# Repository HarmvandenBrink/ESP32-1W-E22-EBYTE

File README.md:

# ESP32 1W E22-400M30S / E22-900M30S
ESP32-based EBYTE E22-400M30S / E22-900M30S compatible 1 Watt board

Forked the design, changed it to KiCAD.

## Features:
* Fully compatible with https://github.com/G4lile0/ESP32-OLED-Fossa-GroundStation
* Radio: Ebyte E22-400M30S / E22-900M30S (http://www.ebyte.com/en/product-view-news.aspx?id=454)
  * SX1268 with TCXO
  * 1W external PA
  * Automatic Rx/Tx switching
  * IPX and SMA connectors
* OLED display
* Selectable power source (USB/external jack)
* Status LEDs: power, Rx/Tx, ESP32 IO2
* On-board USB/UART convertor

Forked from https://github.com/jgromes/ESP32-1W-GroundStation which was Eagle

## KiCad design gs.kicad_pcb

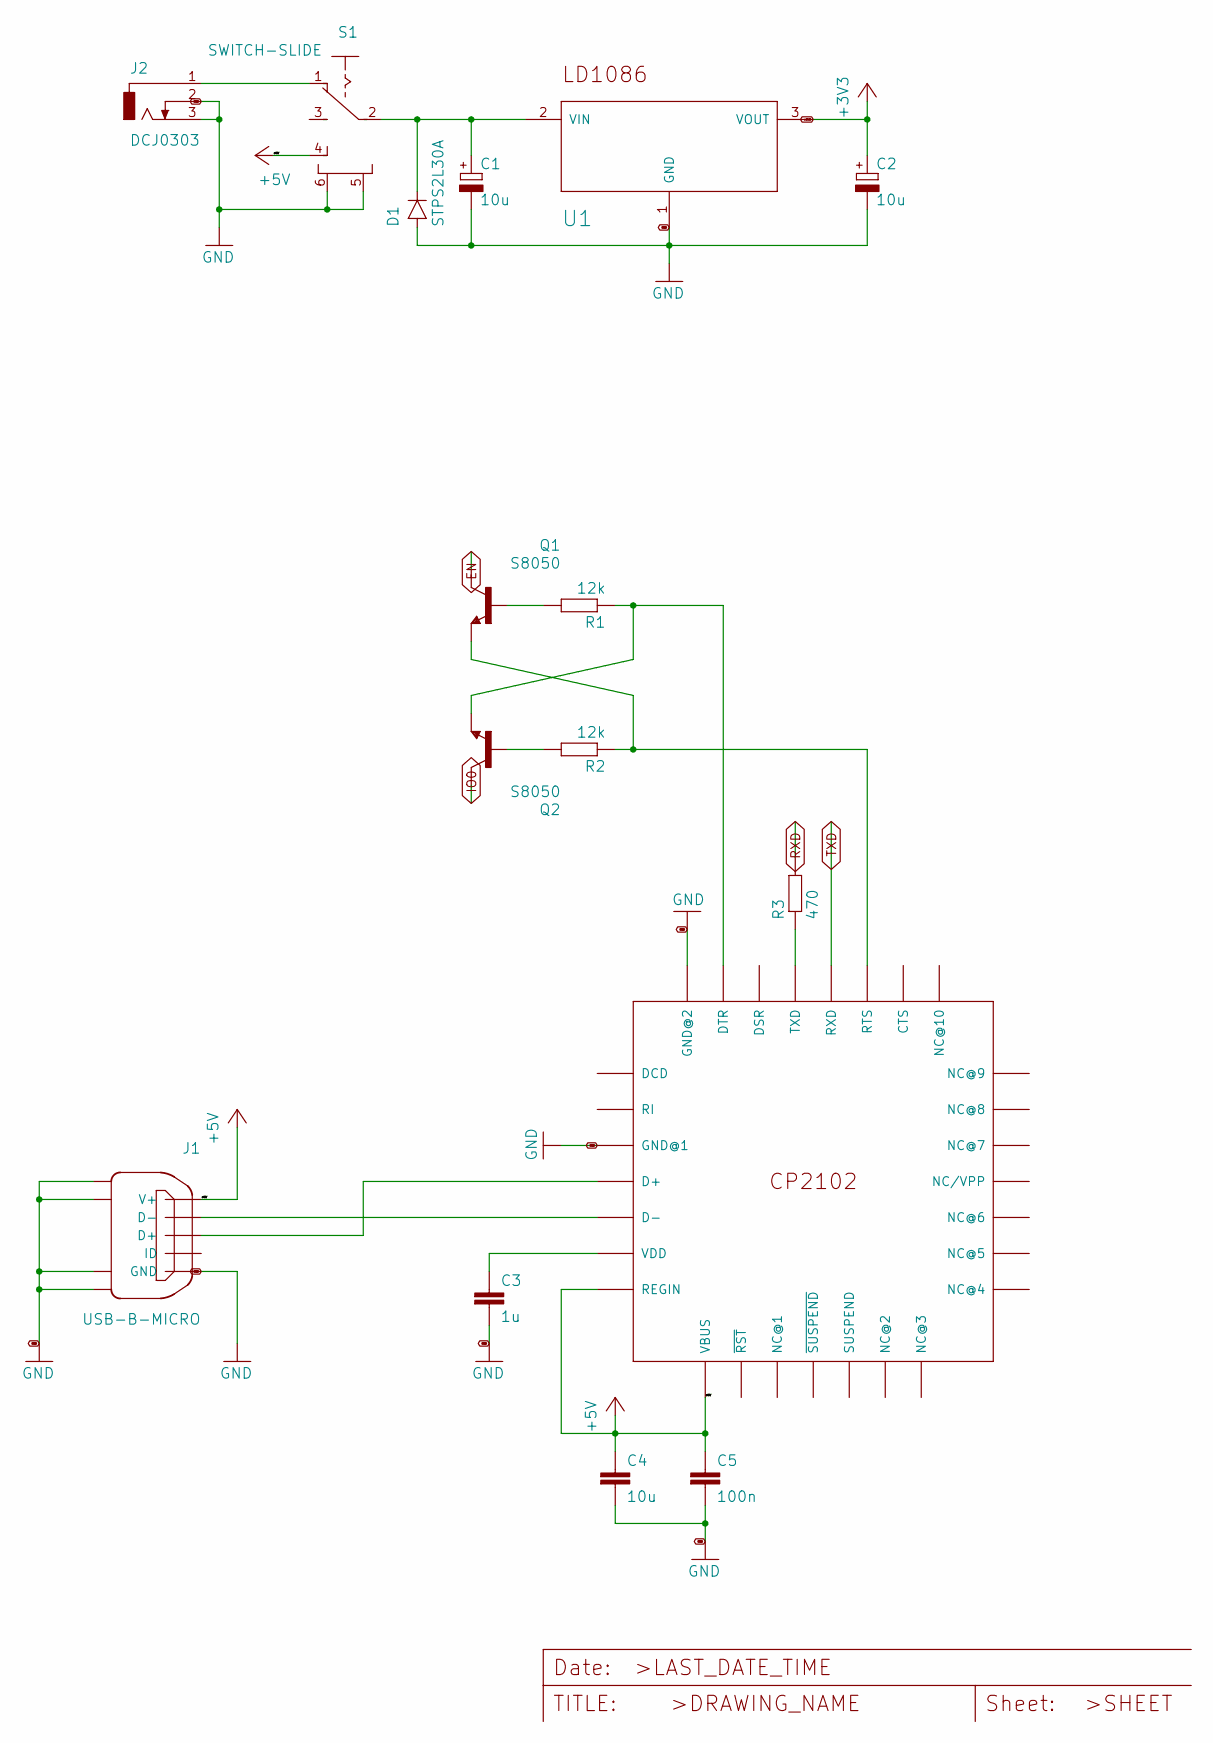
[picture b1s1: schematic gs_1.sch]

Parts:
C1, C2: 10u; SMC_C
C3: 1u; C0805
C4: 10u; C0805
C5: 100n; C0805
D1: STPS2L30A; DIOM4225X245N
J1: USB-B-MICRO
J2: DCJ0303
Q1, Q2: S8050; SOT95P237X110-3N
R1, R2: 12k; R0805
R3: 470; R0805
S1: SWITCH-SLIDE
U1: LD1086DT33TR; TO228P972X240-3N
U2: CP2102; QFN50P500X500X100-29T300N

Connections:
+3V3: C2.+, U1.3 (VOUT); also elsewhere on the board
+5V: C4.1, C5.1, J1.1 (V+), S1.4, U2.7 (REGIN), U2.8 (VBUS)
EN: Q1.3 (C); also elsewhere on the board
GND: C1.-, C2.-, C3.2, C4.2, C5.2, D1.2 (A), J1.5 (GND), J1.6, J1.7, J1.8, J1.9, J2.2, J2.3, S1.5 (S1), S1.6 (S2), U1.1 (GND), U2.3 (GND@1), U2.29 (GND@2); also elsewhere on the board
IO0: Q2.3 (C); also elsewhere on the board
unnamed: C1.+, D1.1 (C), S1.2, U1.2 (VIN)
unnamed: C3.1, U2.6 (VDD)
unnamed: J1.2 (D-), U2.5 (D-)
unnamed: J1.3 (D+), U2.4 (D+)
unnamed: J2.1, S1.1
unnamed: Q1.1 (B), R1.2
unnamed: Q1.2 (E), R2.1, U2.24 (RTS)
unnamed: Q2.1 (B), R2.2
unnamed: Q2.2 (E), R1.1, U2.28 (DTR)
unnamed: R3.1, U2.26 (TXD)
RXD: R3.2; also elsewhere on the board
TXD: U2.25 (RXD); also elsewhere on the board

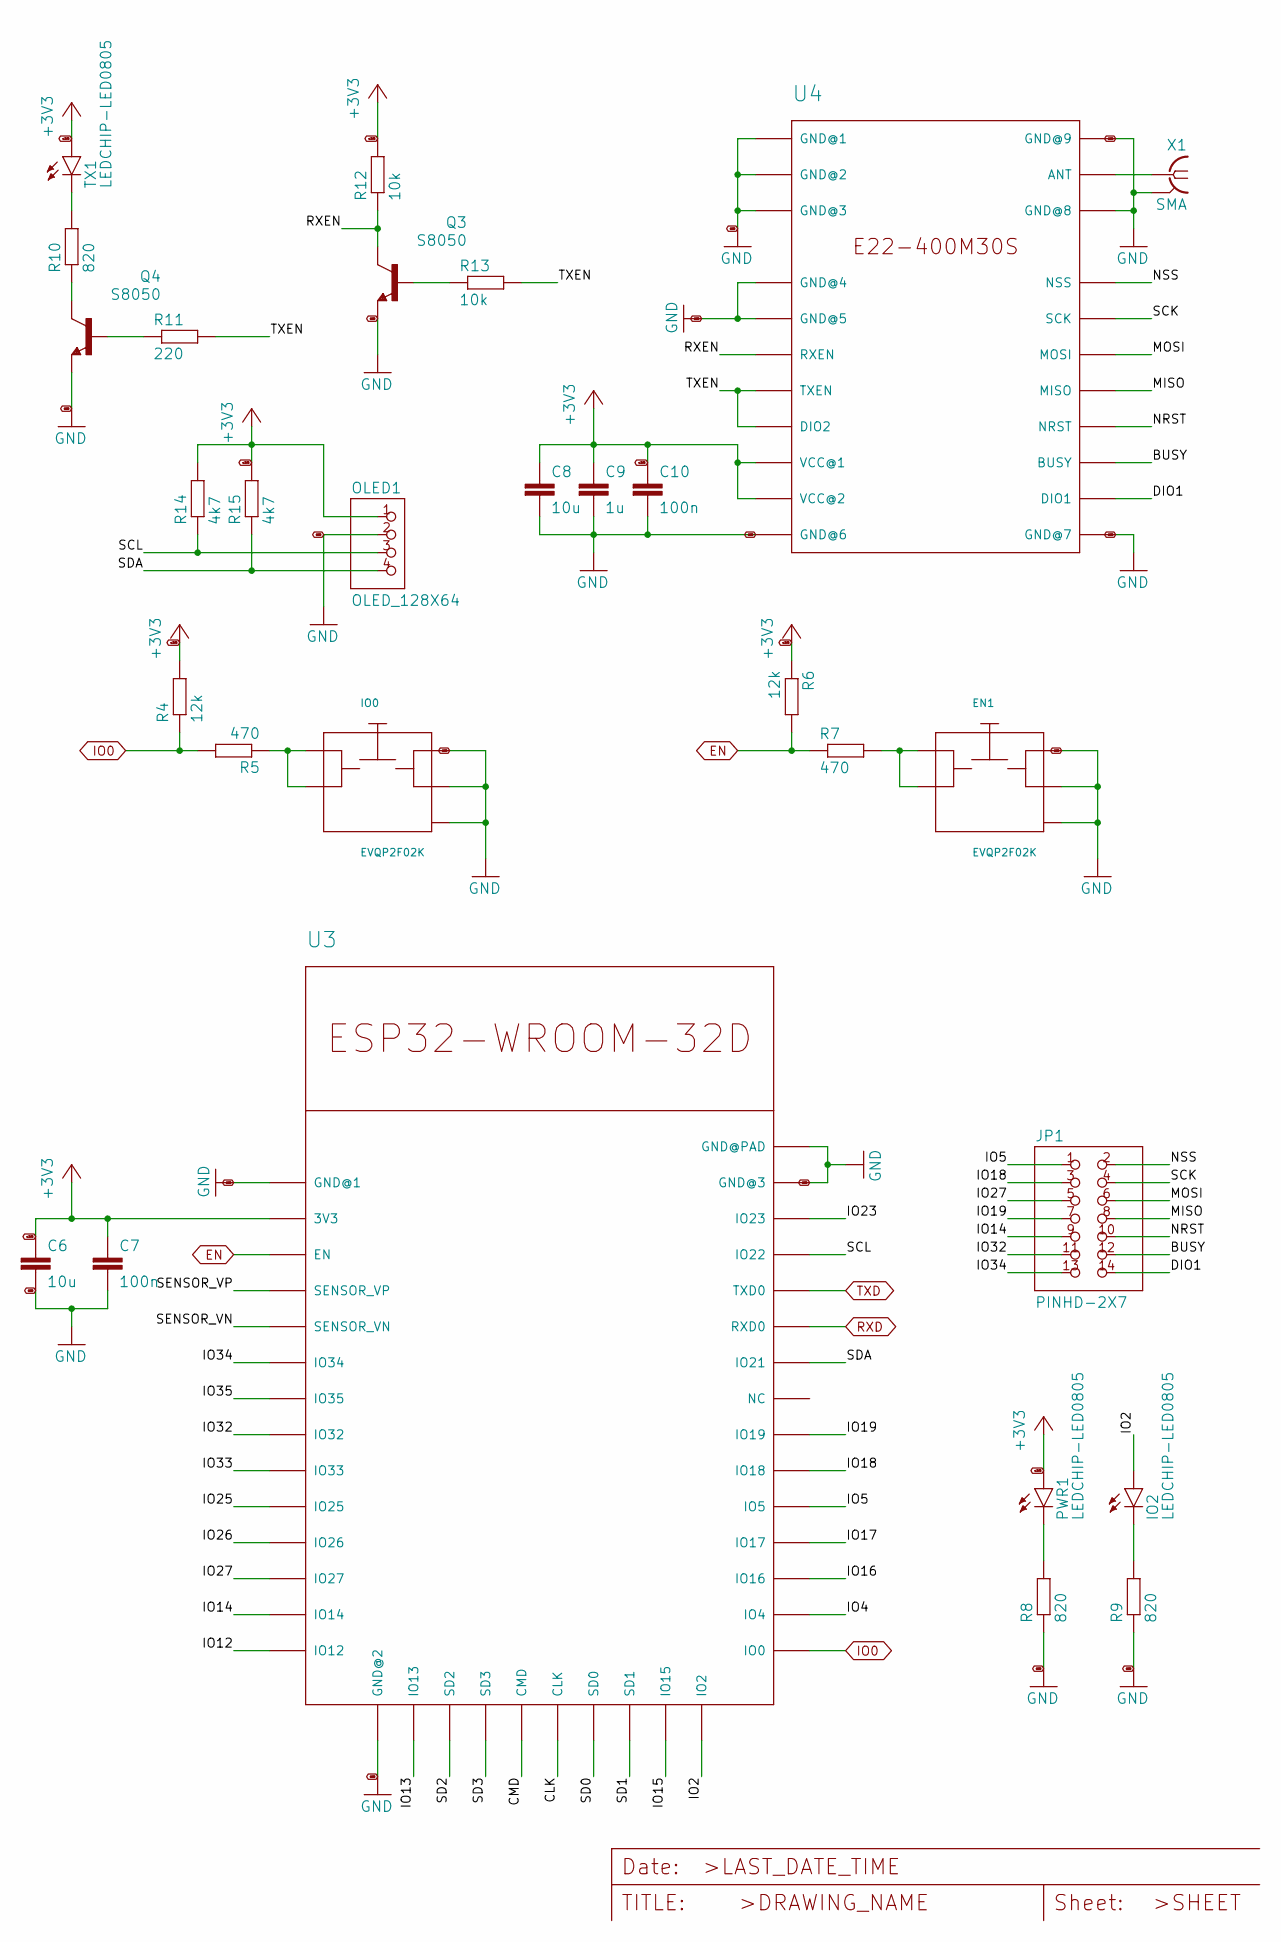
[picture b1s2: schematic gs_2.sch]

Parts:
C6, C8: 10u; C0805
C7, C10: 100n; C0805
C9: 1u; C0805
EN: EVQP2F02K
IO0: EVQP2F02K
IO2: LEDCHIP-LED0805; CHIP-LED0805
JP1: PINHD-2X7; 2X07
OLED: OLED_128X64
PWR: LEDCHIP-LED0805; CHIP-LED0805
Q3, Q4: S8050; SOT95P237X110-3N
R4, R6: 12k; R0805
R5, R7: 470; R0805
R8, R9, R10: 820; R0805
R11: 220; R0805
R12, R13: 10k; R0805
R14, R15: 4k7; R0805
TX: LEDCHIP-LED0805; CHIP-LED0805
U3: ESP32-WROOM-32D; ESP32-SOLO-1
U4: E22-400M30S
X1: SMA

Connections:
+3V3: C6.1, C7.1, C8.1, C9.1, C10.1, R4.2, R6.1, R12.2, R14.2, R15.2, U3.2 (3V3), U4.9 (VCC@1), U4.10 (VCC@2); also elsewhere on the board
/gs_2/BUSY: JP1.12, U4.14 (BUSY)
/gs_2/CLK: U3.20 (CLK)
/gs_2/CMD: U3.19 (CMD)
/gs_2/DIO1: JP1.14, U4.13 (DIO1)
/gs_2/IO2: IO2.A, U3.24 (IO2)
/gs_2/IO4: U3.26 (IO4)
/gs_2/IO5: JP1.1, U3.29 (IO5)
/gs_2/IO12: U3.14 (IO12)
/gs_2/IO13: U3.16 (IO13)
/gs_2/IO14: JP1.9, U3.13 (IO14)
/gs_2/IO15: U3.23 (IO15)
/gs_2/IO16: U3.27 (IO16)
/gs_2/IO17: U3.28 (IO17)
/gs_2/IO18: JP1.3, U3.30 (IO18)
/gs_2/IO19: JP1.7, U3.31 (IO19)
/gs_2/IO23: U3.37 (IO23)
/gs_2/IO25: U3.10 (IO25)
/gs_2/IO26: U3.11 (IO26)
/gs_2/IO27: JP1.5, U3.12 (IO27)
/gs_2/IO32: JP1.11, U3.8 (IO32)
/gs_2/IO33: U3.9 (IO33)
/gs_2/IO34: JP1.13, U3.6 (IO34)
/gs_2/IO35: U3.7 (IO35)
/gs_2/MISO: JP1.8, U4.16 (MISO)
/gs_2/MOSI: JP1.6, U4.17 (MOSI)
/gs_2/NRST: JP1.10, U4.15 (NRST)
/gs_2/NSS: JP1.2, U4.19 (NSS)
/gs_2/RXEN: Q3.3 (C), R12.1, U4.6 (RXEN)
/gs_2/SCK: JP1.4, U4.18 (SCK)
/gs_2/SCL: R14.1, U3.36 (IO22); also elsewhere on the board
/gs_2/SD0: U3.21 (SD0)
/gs_2/SD1: U3.22 (SD1)
/gs_2/SD2: U3.17 (SD2)
/gs_2/SD3: U3.18 (SD3)
/gs_2/SDA: R15.1, U3.33 (IO21); also elsewhere on the board
/gs_2/SENSOR_VN: U3.5 (SENSOR_VN)
/gs_2/SENSOR_VP: U3.4 (SENSOR_VP)
/gs_2/TXEN: R11.2, R13.2, U4.7 (TXEN), U4.8 (DIO2)
EN: R6.2, R7.1, U3.3 (EN); also elsewhere on the board
GND: C6.2, C7.2, C8.2, C9.2, C10.2, IO0.3, IO0.4, IO0.5, Q3.2 (E), Q4.2 (E), R8.1, R9.1, U3.1 (GND@1), U3.15 (GND@2), U3.38 (GND@3), U3.39 (GND@PAD), U4.1 (GND@1), U4.2 (GND@2), U4.3 (GND@3), U4.4 (GND@4), U4.5 (GND@5), U4.11 (GND@6), U4.12 (GND@7), U4.20 (GND@8), U4.22 (GND@9), X1.G@1 (2), X1.G@2 (2), X1.G@3 (2), X1.G@4 (2); also elsewhere on the board
IO0: R4.1, R5.2, U3.25 (IO0); also elsewhere on the board
unnamed 45: R7.2; also elsewhere on the board
unnamed: IO0.1, IO0.2, R5.1
unnamed: IO2.C, R9.2
unnamed 52: R8.2; also elsewhere on the board
unnamed: Q3.1 (B), R13.1
unnamed: Q4.1 (B), R11.1
unnamed: Q4.3 (C), R10.1
unnamed 61: R10.2; also elsewhere on the board
unnamed: U4.21 (ANT), X1.1
RXD: U3.34 (RXD0); also elsewhere on the board
TXD: U3.35 (TXD0); also elsewhere on the board

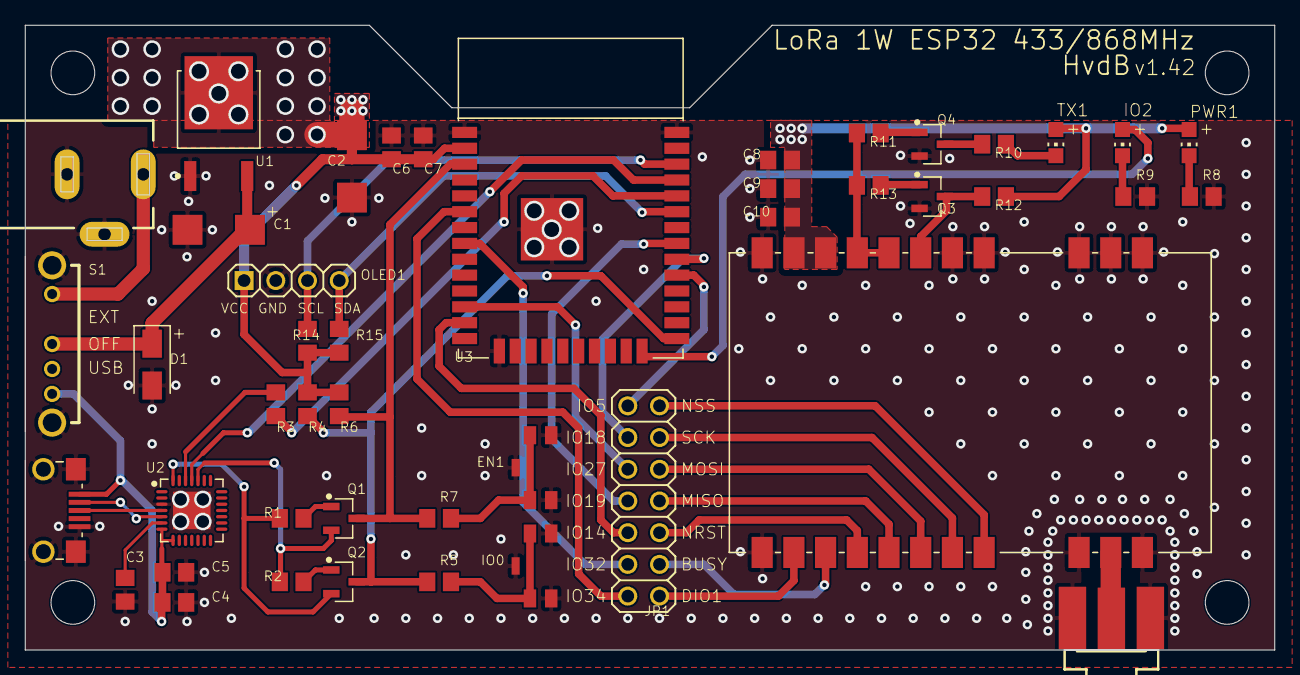
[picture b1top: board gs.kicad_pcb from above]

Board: 2 copper layers, 100.1 x 50.0 mm, 49 parts (0 on the bottom side), 45 nets.

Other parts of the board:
@HOLE0, @HOLE1, @HOLE2, @HOLE3: (no value)
EN1: EVQP2F02K
OLED1: OLED_128X64
PWR1: LEDCHIP-LED0805; CHIP-LED0805
TX1: LEDCHIP-LED0805; CHIP-LED0805

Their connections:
+3V3: OLED1.1, PWR1.A, TX1.A; also elsewhere on the board
/gs_2/SCL: OLED1.3; also elsewhere on the board
/gs_2/SDA: OLED1.4; also elsewhere on the board
GND: EN1.3, EN1.4, EN1.5, OLED1.2; also elsewhere on the board
unnamed 45: EN1.1, EN1.2; also elsewhere on the board
unnamed 52: PWR1.C; also elsewhere on the board
unnamed 61: TX1.C; also elsewhere on the board
